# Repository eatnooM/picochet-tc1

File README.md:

# Picochet-TC1

A dedicated microcontroller board for use with the OpenFIRE firmware, tailored to fit in a Namco Time Crisis 1-3 or Point Blank arcade gun.

The goal of this project is to allow for clean builds in these guns while retaining support for driving the gun's solenoid
(not a big fan of multiple boards floating around in the shell)
and to serve as a base for future Picochet boards in other light guns where a carrier board using a Raspberry Pi Pico or similar would be tricky or impossible.

## Thanks

OpenFIRE project - https://openfirelightgun.org/

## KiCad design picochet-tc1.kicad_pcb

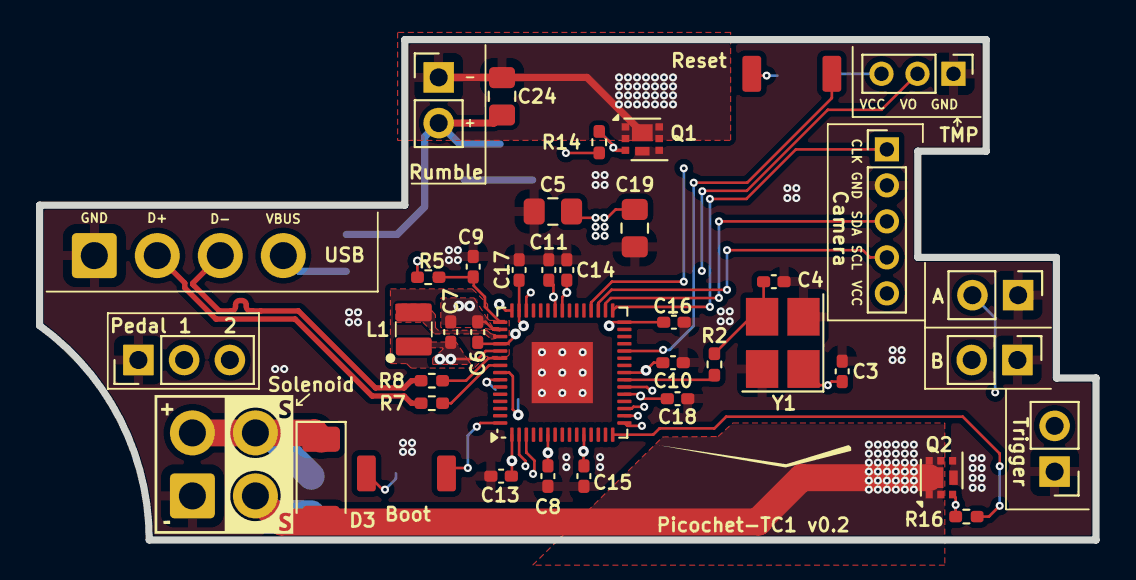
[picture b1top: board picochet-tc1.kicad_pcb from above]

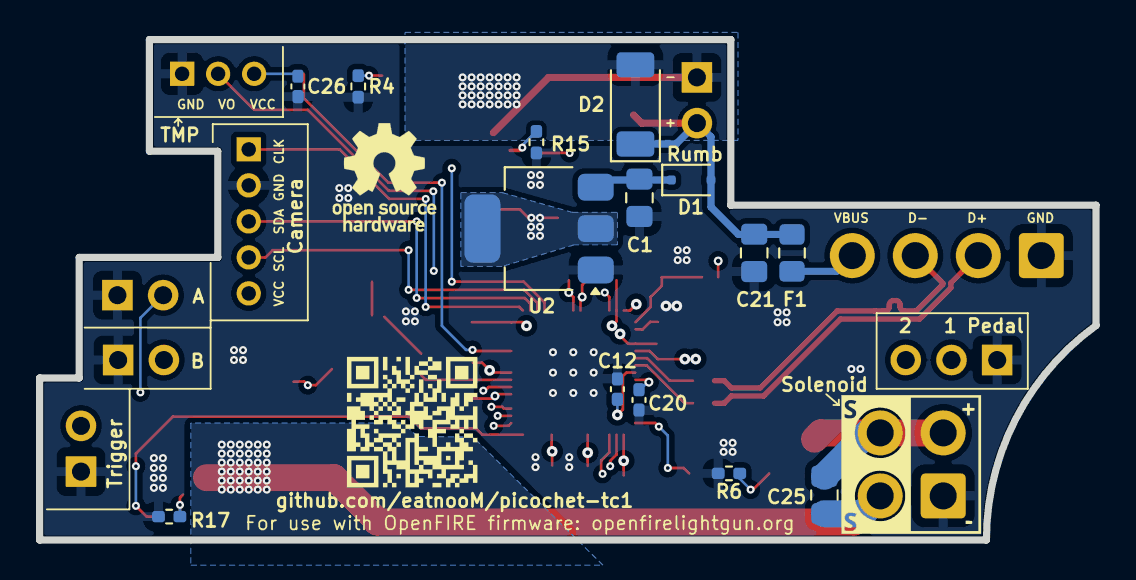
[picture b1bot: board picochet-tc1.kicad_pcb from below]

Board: 4 copper layers, 58.7 x 27.8 mm, 55 parts (15 on the bottom side), 35 nets.

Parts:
C1, C5, C19, C21: 10uF; C_0805_2012Metric_Pad1.18x1.45mm_HandSolder
C3, C4: 15pF; C_0402_1005Metric_Pad0.74x0.62mm_HandSolder
C6, C7, C9, C10: 4.7uF; C_0402_1005Metric_Pad0.74x0.62mm_HandSolder
C8, C11, C12, C13, C14, C15, C16, C17, C18, C20, C26: 100nF; C_0402_1005Metric_Pad0.74x0.62mm_HandSolder
C24, C25: 100nF; C_0805_2012Metric_Pad1.18x1.45mm_HandSolder
D1: D_Schottky; D_SOD-323F
D2, D3: RBR3LAM60B; D_SOD-128
F1: PPTC-6V 500mA; Fuse_0805_2012Metric_Pad1.15x1.40mm_HandSolder
J1, J2, J4, J9: Conn_01x02; PinHeader_1x02_P2.54mm_Vertical
J3: Conn_01x04; USB-PTH-2.5MMOD-3.5mmSpacing
J5: Conn_02x02; 02x02_PTH-2.5MMOD-3.5mmSpacing
J6: Conn_01x05; PinHeader_1x05_P2.00mm_Vertical
J7: Conn_01x03; PinHeader_1x03_P2.00mm_Vertical
J8: Conn_01x03; PinHeader_1x03_P2.54mm_Vertical
L1: AOTA-B201610S3R3; L_0806_PolarityMark
Q1, Q2: DMT12H060LFDF; Diodes_UDFN2020-6_Type-F
QR*****: github.com/eatnooM/picochet-tc1; picochet-tc1-repo-qr
R2, R4, R6, R14, R16: 1K; R_0402_1005Metric_Pad0.72x0.64mm_HandSolder
R5: 33R; R_0402_1005Metric_Pad0.72x0.64mm_HandSolder
R7, R8: 27R; R_0402_1005Metric_Pad0.72x0.64mm_HandSolder
R15, R17: 100K; R_0402_1005Metric_Pad0.72x0.64mm_HandSolder
SW1, SW2: SW_Push; Switch-Push-SMD-4mmx3mm
U1: RP2354A; QFN-60-1EP_7x7mm_P0.4mm_EP3.4x3.4mm
U2: NCP1117-3.3_SOT223; SOT-223-3_TabPin2
Y1: ABM8-272-T3; Crystal_SMD_3225-4Pin_3.2x2.5mm_HandSoldering

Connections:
+1V1: C7.2, C8.2, C10.2, C11.2, L1.1, U1.6 (DVDD), U1.23 (DVDD), U1.39 (DVDD), U1.50 (VREG_FB)
+3V3: C5.1, C6.2, C12.2, C13.2, C14.2, C15.2, C16.2, C17.1, C18.2, C19.1, C20.2, C26.1, J6.5, J7.3, R5.1, U1.1 (IOVDD), U1.11 (IOVDD), U1.20 (IOVDD), U1.30 (IOVDD), U1.38 (IOVDD), U1.44 (ADC_AVDD), U1.45 (IOVDD), U1.49 (VREG_VIN), U1.53 (USB_OTP_VDD), U1.54 (QSPI_IOVDD), U2.2 (VO)
+5V: C21.1, C24.2, D1.2 (A), D2.1 (K), F1.2, J1.2
/CAM_CLK: J6.1, U1.31 (GPIO19)
/CAM_SCL: J6.4, U1.33 (GPIO21)
/CAM_SDA: J6.3, U1.32 (GPIO20)
/RMB_GND: C24.1, D2.2 (A), J1.1, Q1.1 (D), Q1.2 (D), Q1.5 (D), Q1.6 (D), Q1.7 (D)
/RUMBLE: R14.1, U1.34 (GPIO22)
/SOLENOID: R16.1, U1.15 (GPIO11)
/SOL_GND: C25.1, D3.2 (A), J5.2, Q2.1 (D), Q2.2 (D), Q2.5 (D), Q2.6 (D), Q2.7 (D)
/TMP: J7.2, U1.43 (GPIO29/ADC3)
/USB_D+: J3.2, R7.1
/USB_D-: J3.3, R8.1
/VREG_LX: L1.2, U1.48 (VREG_LX)
/~BTN_A: J4.2, U1.17 (GPIO13)
/~BTN_B: J9.2, U1.18 (GPIO14)
/~BTN_PEDAL_1: J8.2, U1.2 (GPIO0)
/~BTN_PEDAL_2: J8.3, U1.3 (GPIO1)
/~BTN_TRIGGER: J2.2, U1.16 (GPIO12)
/~RESET: SW2.2, U1.26 (RUN)
GND: C1.2, C3.1, C4.1, C5.2, C6.1, C7.1, C8.1, C9.1, C10.1, C11.1, C12.1, C13.1, C14.1, C15.1, C16.1, C17.2, C18.1, C19.2, C20.1, C21.2, C26.2, J2.1, J3.1, J4.1, J5.1, J6.2, J7.1, J8.1, J9.1, Q1.4 (S), Q1.8 (S), Q2.4 (S), Q2.8 (S), R4.1, R6.1, R15.1, R17.1, U1.47 (VREG_PGND), U1.61 (GND), U2.1 (GND), Y1.2 (G), Y1.4 (G)
unnamed: C4.2, R2.1, Y1.3
unnamed: Q1.3 (G), R14.2, R15.2
unnamed: Q2.3 (G), R16.2, R17.2
unnamed: R4.2, SW2.1
unnamed: R6.2, SW1.1
unnamed: R8.2, U1.51 (USB_DM)
unnamed: R7.2, U1.52 (USB_DP)
unnamed: C3.2, U1.21 (XIN), Y1.1
unnamed: R2.2, U1.22 (XOUT)
unnamed: SW1.2, U1.60 (~QSPI_SS)
SOL_PWR: C25.2, D3.1 (K), J5.3, J5.4
VBUS: F1.1, J3.4
VREG_AVDD: C9.2, R5.2, U1.46 (VREG_AVDD)
VSYS: C1.1, D1.1 (K), U2.3 (VI)

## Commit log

2026-02-15 Cleanup
2026-02-15 Add QR link to repo, cleanup
2026-02-17 Small tweaks for v0.1 prototype
2026-02-20 Larger vias to keep JLC happy
2026-02-20 swap 10uF caps to 0805; tweak routing
2026-05-04 Add options for second pedal and A/B buttons
2026-05-04 Add license
2026-05-10 Add BOM
2026-05-10 Fix LCSC part numbers for some components
